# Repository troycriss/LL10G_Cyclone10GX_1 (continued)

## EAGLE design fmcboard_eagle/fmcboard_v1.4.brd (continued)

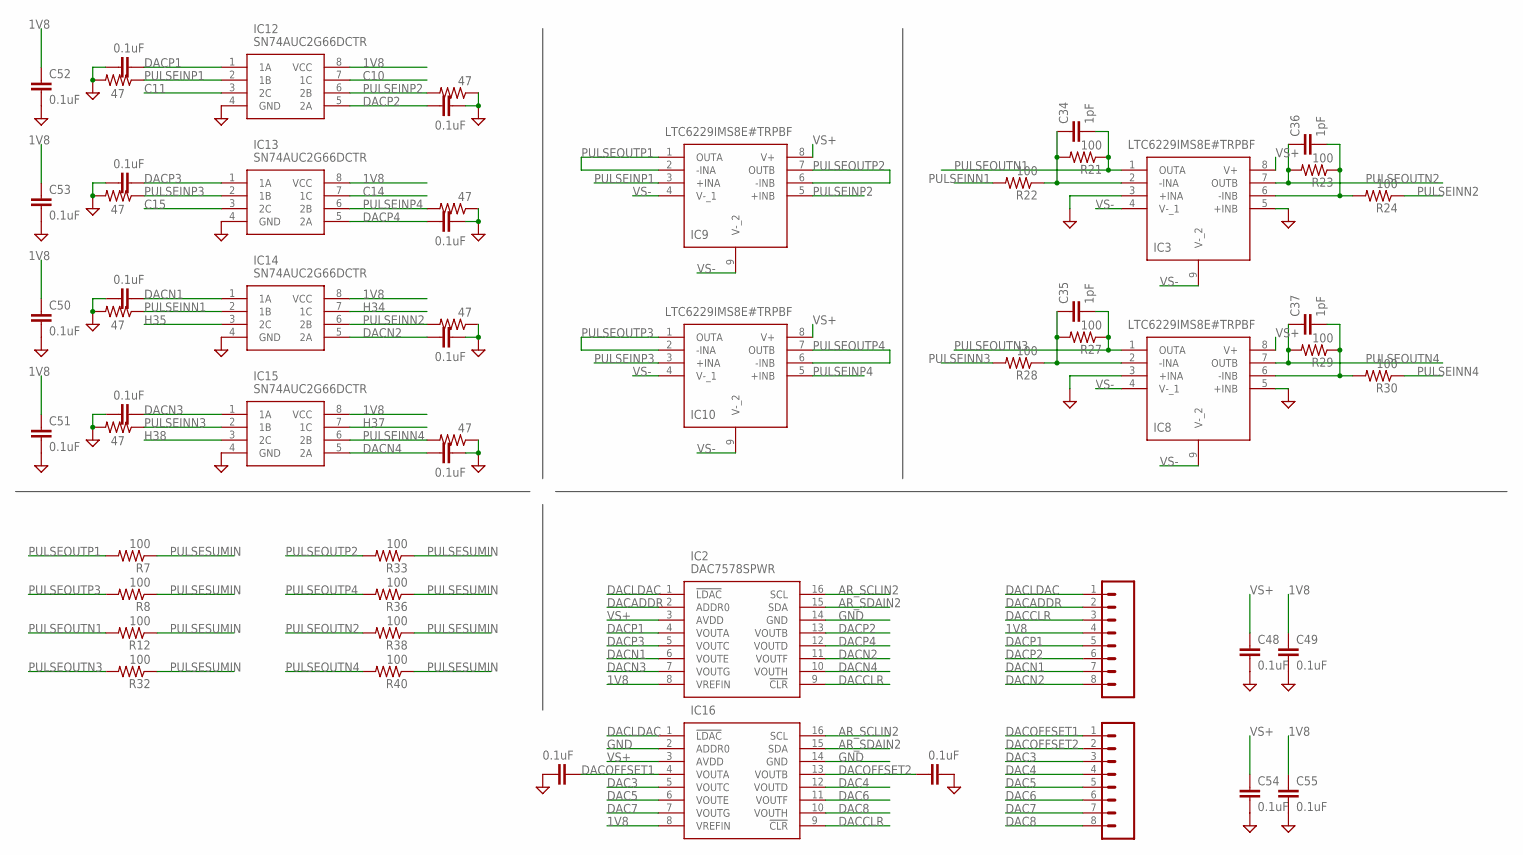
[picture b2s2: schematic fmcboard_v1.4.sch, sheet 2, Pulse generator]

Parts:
C34, C35, C36, C37: 1pF; 0805
C48, C49, C50, C51, C52, C53, C54, C55, C56, C57, C58, C59, C60, C61, C62, C63, C64, C65: 0.1uF; 0805
IC2, IC16: DAC7578SPWR; SOP65P640X120-16N
IC3, IC8, IC9, IC10: LTC6229IMS8E#TRPBF; SOP65P490X110-9N
IC12, IC13, IC14, IC15: SN74AUC2G66DCTR; SOP65P400X130-8N
J9, J10: 8pin; 1X08
R7, R8, R12, R21, R22, R23, R24, R27, R28, R29, R30, R32, R33, R36, R38, R40: 100; R0805
R37, R39, R41, R43, R44, R45, R46, R47: 47; R0805

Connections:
1V8: C49.1, C50.1, C51.1, C52.1, C53.1, C55.1, IC2.8 (VREFIN), IC12.8 (VCC), IC13.8 (VCC), IC14.8 (VCC), IC15.8 (VCC), IC16.8 (VREFIN), J9.4; also elsewhere on the board
AR_SCLIN2: IC2.16 (SCL), IC16.16 (SCL); also elsewhere on the board
AR_SDAIN2: IC2.15 (SDA), IC16.15 (SDA); also elsewhere on the board
C10: IC12.7 (1C); also elsewhere on the board
C11: IC12.3 (2C); also elsewhere on the board
C14: IC13.7 (1C); also elsewhere on the board
C15: IC13.3 (2C); also elsewhere on the board
DAC3: IC16.5 (VOUTC), J10.3
DAC4: IC16.12 (VOUTD), J10.4
DAC5: IC16.6 (VOUTE), J10.5
DAC6: IC16.11 (VOUTF), J10.6
DAC7: IC16.7 (VOUTG), J10.7
DAC8: IC16.10 (VOUTH), J10.8
DACADDR: IC2.2 (ADDR0), J9.2
DACCLR: IC2.9 (!CLR), IC16.9 (!CLR), J9.3
DACLDAC: IC2.1 (!LDAC), IC16.1 (!LDAC), J9.1
DACN1: C57.2, IC2.6 (VOUTE), IC14.1 (1A), J9.7
DACN2: C61.1, IC2.11 (VOUTF), IC14.5 (2A), J9.8
DACN3: C59.2, IC2.7 (VOUTG), IC15.1 (1A)
DACN4: C60.1, IC2.10 (VOUTH), IC15.5 (2A)
DACOFFSET1: C64.2, IC16.4 (VOUTA), J10.1; also elsewhere on the board
DACOFFSET2: C65.1, IC16.13 (VOUTB), J10.2; also elsewhere on the board
DACP1: C58.2, IC2.4 (VOUTA), IC12.1 (1A), J9.5
DACP2: C63.1, IC2.13 (VOUTB), IC12.5 (2A), J9.6
DACP3: C56.2, IC2.5 (VOUTC), IC13.1 (1A)
DACP4: C62.1, IC2.12 (VOUTD), IC13.5 (2A)
GND: C48.2, C49.2, C50.2, C51.2, C52.2, C53.2, C54.2, C55.2, C56.1, C57.1, C58.1, C59.1, C60.2, C61.2, C62.2, C63.2, C64.1, C65.2, IC2.14 (GND), IC3.3 (+INA), IC3.5 (+INB), IC8.3 (+INA), IC8.5 (+INB), IC12.4 (GND), IC13.4 (GND), IC14.4 (GND), IC15.4 (GND), IC16.2 (ADDR0), IC16.14 (GND), R37.1, R39.2, R41.1, R43.2, R44.2, R45.2, R46.1, R47.1; also elsewhere on the board
H34: IC14.7 (1C); also elsewhere on the board
H35: IC14.3 (2C); also elsewhere on the board
H37: IC15.7 (1C); also elsewhere on the board
H38: IC15.3 (2C); also elsewhere on the board
unnamed: C36.2, IC3.6 (-INB), R23.1, R24.2
unnamed: C35.1, IC8.2 (-INA), R27.2, R28.1
unnamed: C34.1, IC3.2 (-INA), R21.2, R22.1
unnamed: C37.2, IC8.6 (-INB), R29.1, R30.2
PULSEINN1: IC14.2 (1B), R22.2, R44.1
PULSEINN2: IC14.6 (2B), R24.1, R47.2
PULSEINN3: IC15.2 (1B), R28.2, R45.1
PULSEINN4: IC15.6 (2B), R30.1, R46.2
PULSEINP1: IC9.3 (+INA), IC12.2 (1B), R39.1
PULSEINP2: IC9.5 (+INB), IC12.6 (2B), R37.2
PULSEINP3: IC10.3 (+INA), IC13.2 (1B), R43.1
PULSEINP4: IC10.5 (+INB), IC13.6 (2B), R41.2
PULSEOUTN1: C34.2, IC3.1 (OUTA), R12.2, R21.1
PULSEOUTN2: C36.1, IC3.7 (OUTB), R23.2, R38.2
PULSEOUTN3: C35.2, IC8.1 (OUTA), R27.1, R32.2
PULSEOUTN4: C37.1, IC8.7 (OUTB), R29.2, R40.2
PULSEOUTP1: IC9.1 (OUTA), IC9.2 (-INA), R7.2
PULSEOUTP2: IC9.6 (-INB), IC9.7 (OUTB), R33.2
PULSEOUTP3: IC10.1 (OUTA), IC10.2 (-INA), R8.2
PULSEOUTP4: IC10.6 (-INB), IC10.7 (OUTB), R36.2
PULSESUMIN: R7.1, R8.1, R12.1, R32.1, R33.1, R36.1, R38.1, R40.1; also elsewhere on the board
VS+: C48.1, C54.1, IC2.3 (AVDD), IC3.8 (V+), IC8.8 (V+), IC9.8 (V+), IC10.8 (V+), IC16.3 (AVDD); also elsewhere on the board
VS-: IC3.4 (V-_1), IC3.9 (V-_2), IC8.4 (V-_1), IC8.9 (V-_2), IC9.4 (V-_1), IC9.9 (V-_2), IC10.4 (V-_1), IC10.9 (V-_2); also elsewhere on the board

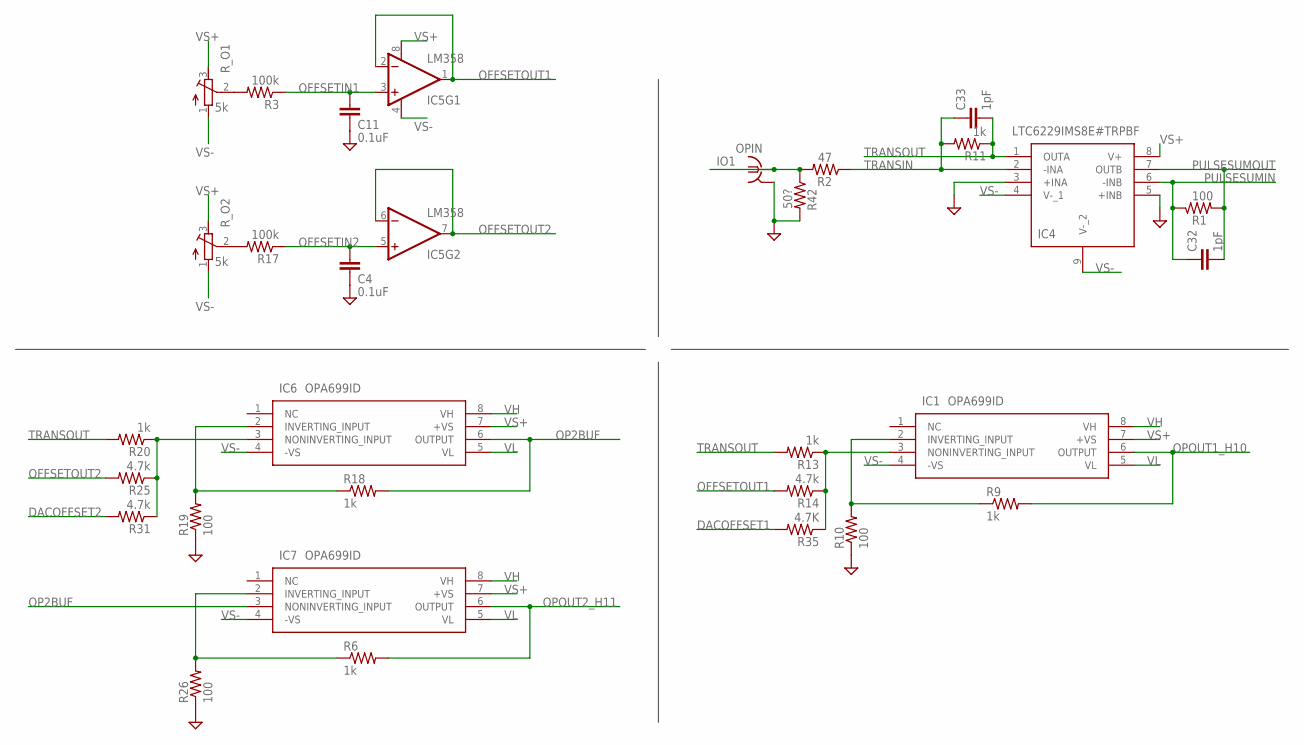
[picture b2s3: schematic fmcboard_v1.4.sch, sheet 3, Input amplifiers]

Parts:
C4, C11: 0.1uF; 0805
C32, C33: 1pF; 0805
IC1, IC6, IC7: OPA699ID; SOIC127P600X175-8N
IC4: LTC6229IMS8E#TRPBF; SOP65P490X110-9N
IC5: LM358; DIP08
OPIN: BU-SMB-V
R1, R10, R19, R26: 100; R0805
R2: 47; R0805
R3, R17: 100k; R0805
R6, R9, R11, R13, R18, R20: 1k; R0805
R14, R25, R31: 4.7k; R0805
R35: 4.7K; R0805
R42: 50?; R0805
R_O1, R_O2: 5k; RTRIM3296W

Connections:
DACOFFSET1: R35.2; also elsewhere on the board
DACOFFSET2: R31.2; also elsewhere on the board
GND: C4.2, C11.2, IC4.3 (+INA), IC4.5 (+INB), OPIN.2, OPIN.3 (2), OPIN.4 (2), OPIN.5 (2), R10.1, R19.1, R26.1, R42.2; also elsewhere on the board
IO1: OPIN.1, R2.2, R42.1; also elsewhere on the board
unnamed: IC1.3 (NONINVERTING_INPUT), R13.1, R14.1, R35.1
unnamed: R17.2, R_O2.2 (S)
unnamed: IC1.2 (INVERTING_INPUT), R9.1, R10.2
unnamed: R3.2, R_O1.2 (S)
unnamed: IC6.2 (INVERTING_INPUT), R18.1, R19.2
unnamed: IC6.3 (NONINVERTING_INPUT), R20.1, R25.1, R31.1
unnamed: IC7.2 (INVERTING_INPUT), R6.1, R26.2
OFFSETIN1: C11.1, IC5.3 (+IN), R3.1; also elsewhere on the board
OFFSETIN2: C4.1, IC5.5 (+IN), R17.1; also elsewhere on the board
OFFSETOUT1: IC5.1 (OUT), IC5.2 (-IN), R14.2
OFFSETOUT2: IC5.6 (-IN), IC5.7 (OUT), R25.2
OP2BUF: IC6.6 (OUTPUT), IC7.3 (NONINVERTING_INPUT), R18.2; also elsewhere on the board
OPOUT1_H10: IC1.6 (OUTPUT), R9.2; also elsewhere on the board
OPOUT2_H11: IC7.6 (OUTPUT), R6.2; also elsewhere on the board
PULSESUMIN: C32.1, IC4.6 (-INB), R1.1; also elsewhere on the board
PULSESUMOUT: C32.2, IC4.7 (OUTB), R1.2; also elsewhere on the board
TRANSIN: C33.1, IC4.2 (-INA), R2.1, R11.2
TRANSOUT: C33.2, IC4.1 (OUTA), R11.1, R13.2, R20.2; also elsewhere on the board
VH: IC1.8 (VH), IC6.8 (VH), IC7.8 (VH); also elsewhere on the board
VL: IC1.5 (VL), IC6.5 (VL), IC7.5 (VL); also elsewhere on the board
VS+: IC1.7 (+VS), IC4.8 (V+), IC5.8 (V+), IC6.7 (+VS), IC7.7 (+VS), R_O1.3 (E), R_O2.3 (E); also elsewhere on the board
VS-: IC1.4 (-VS), IC4.4 (V-_1), IC4.9 (V-_2), IC5.4 (V-), IC6.4 (-VS), IC7.4 (-VS), R_O1.1 (A), R_O2.1 (A); also elsewhere on the board

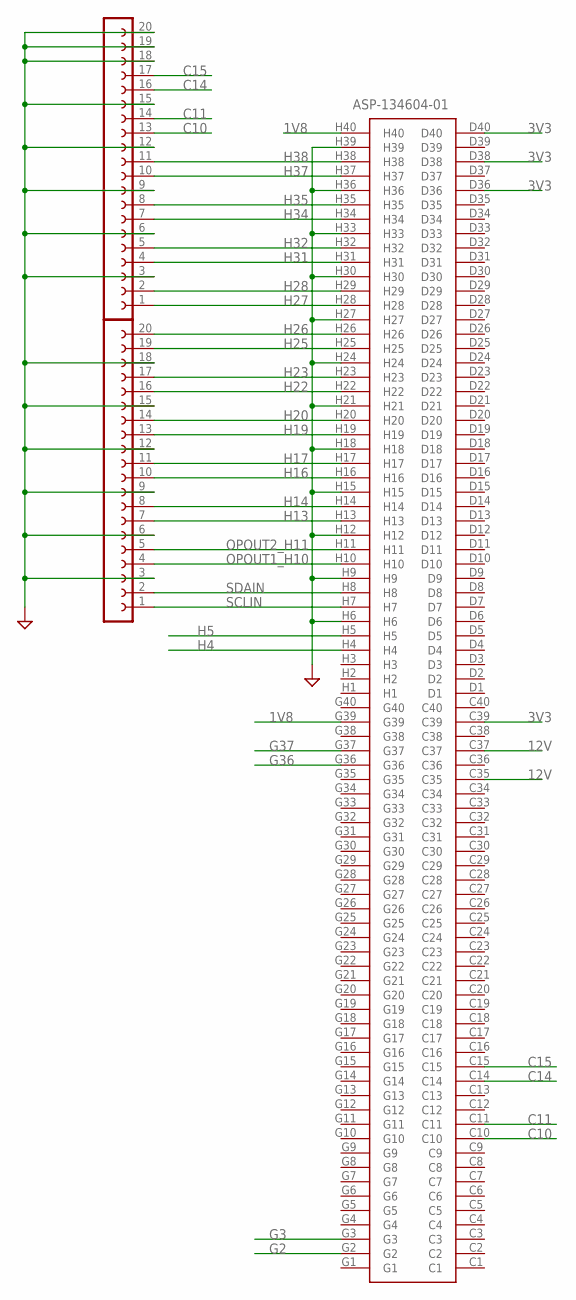
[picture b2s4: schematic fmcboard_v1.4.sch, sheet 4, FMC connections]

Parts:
J2: ASP-134604-01; ASP13460401
SV1, SV2: 20; FE20

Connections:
1V8: J2.G39, J2.H40; also elsewhere on the board
3V3: J2.C39, J2.D36, J2.D38, J2.D40; also elsewhere on the board
12V: J2.C35, J2.C37; also elsewhere on the board
C10: J2.C10, SV2.13; also elsewhere on the board
C11: J2.C11, SV2.14; also elsewhere on the board
C14: J2.C14, SV2.16; also elsewhere on the board
C15: J2.C15, SV2.17; also elsewhere on the board
G2: J2.G2; also elsewhere on the board
G3: J2.G3; also elsewhere on the board
G36: J2.G36; also elsewhere on the board
G37: J2.G37; also elsewhere on the board
GND: J2.H6, J2.H9, J2.H12, J2.H15, J2.H18, J2.H21, J2.H24, J2.H27, J2.H30, J2.H33, J2.H36, J2.H39, SV1.3, SV1.6, SV1.9, SV1.12, SV1.15, SV1.18, SV2.3, SV2.6, SV2.9, SV2.12, SV2.15, SV2.18, SV2.19, SV2.20; also elsewhere on the board
H4: J2.H4; also elsewhere on the board
H5: J2.H5; also elsewhere on the board
H13: J2.H13, SV1.7
H14: J2.H14, SV1.8
H16: J2.H16, SV1.10
H17: J2.H17, SV1.11
H19: J2.H19, SV1.13
H20: J2.H20, SV1.14
H22: J2.H22, SV1.16
H23: J2.H23, SV1.17
H25: J2.H25, SV1.19
H26: J2.H26, SV1.20
H27: J2.H28, SV2.1
H28: J2.H29, SV2.2
H31: J2.H31, SV2.4
H32: J2.H32, SV2.5
H34: J2.H34, SV2.7; also elsewhere on the board
H35: J2.H35, SV2.8; also elsewhere on the board
H37: J2.H37, SV2.10; also elsewhere on the board
H38: J2.H38, SV2.11; also elsewhere on the board
OPOUT1_H10: J2.H10, SV1.4; also elsewhere on the board
OPOUT2_H11: J2.H11, SV1.5; also elsewhere on the board
SCLIN: J2.H7, SV1.1; also elsewhere on the board
SDAIN: J2.H8, SV1.2; also elsewhere on the board

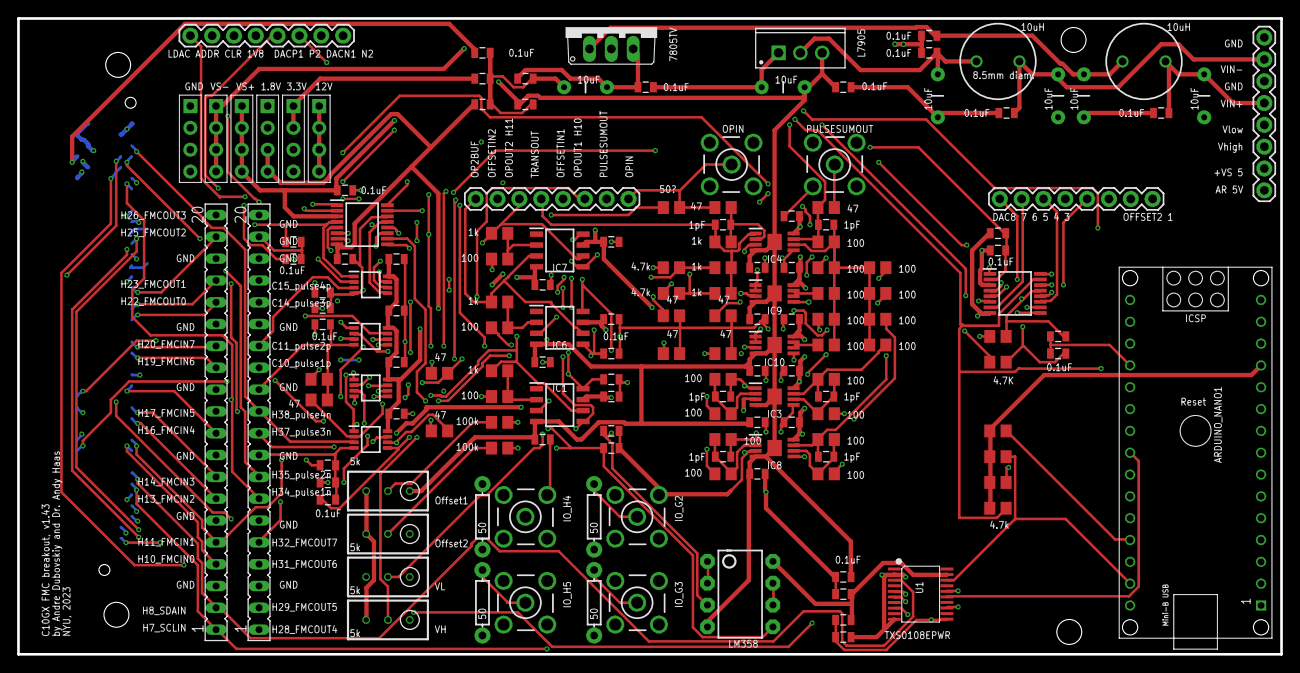
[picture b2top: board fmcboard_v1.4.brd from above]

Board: 4 copper layers, 147.0 x 74.0 mm, 160 parts (1 on the bottom side), 108 nets.

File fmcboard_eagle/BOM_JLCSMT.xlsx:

Comment | Designator | Footprint | JLCPCB Part #（optional）
0.1uF | C3, C4, C5, C6, C7, C8, C9, C10, C11, C12, C13, C14, C15, C16, C17, C18, C19, C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 | 0805
1 | ARDUINO_NANO1 | ARDUINO_NANO
100k | R3, R17 | R0805
10uF | C1, C2, C38, C39, C40, C41 | CAP-PTH-5MM
10uH | L1, L2 | 6000-XXXX-RC
1k | R1, R6, R7, R8, R9, R11, R12, R13, R18, R20, R21, R22, R23, R24, R27, R28, R29,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 | R0805
1pF | C32, C33, C34, C35, C36, C37 | 0805
20 | SV1, SV2 | FE20
100 | R10, R19, R26 | R0805
20k | R_O1, R_O2, R_VH, R_VL | RTRIM3296W
4.7k | R48, R49, R50, R51 | R0805
47 | R37, R39, R41, R43, R44, R45, R46, R47 | R0805
4k | R14, R25, R31, R35 | R0805
4p-2.54 | J3, J4, J6, J7, J8, J12 | H4-2.54
50 | R2, R34 | R0805
50 | R4, R5, R15, R16 | AXIAL-0.3
50? | R42 | R0805
7805TV | IC11 | TO220V
8pin | J1, J5, J9, J10 | 8-pin
ASP-134604-01 | J2 | ASP13460401
BU-SMB-V | IO_G2, IO_G3, IO_H4, IO_H5, OPIN, PULSESUMOUT | BU-SMB-V
DAC7578SPWR | IC2, IC16 | SOP65P640X120-16N
LM358 | IC5 | DIP08
LTC6229IMS8E#TRPBF | IC3, IC4, IC8, IC9, IC10 | SOP65P490X110-9N
OPA699ID | IC1, IC6, IC7 | SOIC127P600X175-8N
SN74AUC2G66DCTR | IC12, IC13, IC14, IC15 | SOP65P400X130-8N
STMICROELECTRONICS_L7905ACVSTMICROELECTRONICS_L7905ACV_0_0 | U2 | STMICROELECTRONICS_L7905ACV_0
TXS0108EPWR | U1 | TSSOP20-0.65-6.5X4.4MM

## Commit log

2023-03-08 turn off tx if pin 2 at gnd
2023-03-08 take 8 inputs from FMC and add to ethernet data
2023-03-09 try adding IP and UDP headers
2023-03-10 count bytes also during ip123
2023-03-10 send ethII header, and fix udp length calculation
2023-03-10 wireshark UDP
2023-03-13 docs
2023-03-13 add sketch of fmcboard
2023-03-13 fifo test
2023-03-13 fifo test 2
2023-03-13 fifo test 3
2023-03-13 fifo test 4
2023-03-13 op amp
2023-03-14 fifo working sort of
2023-03-14 with test data
2023-03-14 opa699 datasheet
2023-03-14 with more clocks
2023-03-14 just need to close timing
2023-03-15 added two op amps to condition input and added GPIO breakout
2023-03-15 ripup'd all routes
2023-03-15 timing closed
2023-03-15 board v1 work with Andre
2023-03-15 Variable IP address
2023-03-16 fix the ip checksum and make the udp one 0 always
2023-03-16 fix the ip checksum more and put seq_num, packet num, and queue length in the data
2023-03-16 Clear fifo at start of data taking
2023-03-16 Send 1516 bytes
2023-03-16 Decode and print
2023-03-16 remove temp files from git
2023-03-16 remove sim files
2023-03-16 sample nbitstosample bits (1 by default)
2023-03-16 first draft of pcb routing
2023-03-16 add output clock at 156.25 MHz / 16, switch eth1 to another 8 inputs
2023-03-16 fmcboard v1 submitted
2023-03-17 fmcboard v1 submitted again, with board outline and stencil
2023-03-19 get ip data length right
2023-03-20 read 1 extra after clearing fifo
2023-03-20 blink
2023-03-20 update pcaps
2023-03-22 remove do_test_data option, and close timing
2023-03-22 add metastability protection to 3 for fifo
2023-03-23 cleanup pin warnings
2023-03-23 pdf of schematic
2023-03-27 add zip
2023-03-27 add i2c lib
2023-03-27 switch sda scl 5v to 1.8
2023-03-28 Board v1.1
2023-03-28 Add fmc doc
2023-03-28 Add sch printout v1.1 board
2023-04-05 switch sda and scl to match board v1.1
2023-04-05 Change resistors and labels
2023-04-06 ignore qws
2023-04-06 Add more power connections to FMC header
2023-04-06 Update resistor values
2023-04-07 add lm358 op amp buffer for offset
2023-04-07 Update gain resistor values
2023-04-08 use bss138 level shifting
2023-04-08 switch to C26 and C27
2023-04-10 Revert "switch to C26 and C27"
    This reverts commit 01cab55b1ab11df4a8fa88617da78cc3c47528a8.
2023-04-10 Revert "use bss138 level shifting"
    This reverts commit dd6467e355429a32c42db6855984b6cad7435a14.
2023-04-11 Label fmc in/out make fmcout0-3 equal to fmcin0-3, for debugging/testing
2023-04-12 v1.2 draft, add transimpedance amp, 2 gains and offsets, pulse outputs, etc.
2023-04-13 Before routing
2023-04-13 v1.2
2023-04-13 v1.2 gerbers
2023-04-13 v1.21 make exposed pads VS- not GND, divide voltage before op amp buffers, add op amp decoupling caps, improve layout
2023-04-13 v1.21
2023-04-19 Add inputs and outputs for FMC v1.21 board
2023-04-25 Fixes for v1.21, amps etc
2023-04-25 Tune the trans amp gain and compensation
2023-04-26 cleaned up a bit, added topgnd cutouts still need to fix power, layout of amp feedback, and route
2023-04-26 did power still need to fix layout of amp feedback, and route
2023-04-26 minor
2023-04-27 most routing done by hand
2023-04-27 v1.3
2023-04-29 Fix feedback compensation caps on neg pulse amps, new footprint for L7905
2023-05-26 added pulsecontroller and console commands to adjust pulse width. Not working yet.
2023-05-31 Added pulse/PulseController.v file and console command for pause duration. Changed assignments in pulser to async. Waveform is no longer "shaky"
2023-05-31 Using slower clock now ("fast1_clk")
2023-06-01 Using faster clock now ("fast2_clk")
2023-06-01 increase udp buff size
2023-06-02 localhost to ""
2023-06-02 LED BUILTING should be an output
2023-06-02 Note ethernet card settings
2023-06-02 Print only 1/100 packets. This keeps up with nbitstosend==1 traffic on 10G.
2023-06-08 Added lots of pulses (12 total). Doesn't work yet.
2023-06-09 fixed 12 pulse generator
2023-06-09 Fix compiler warnings and close timing
2023-06-20 printing out trigger and signal in two columns
2023-06-20 random bit parser and averaging works (slowly)
2023-06-20 bit parser works quickly now, with struct.unpack()
2023-07-06 improved and simplified UDPlistner.py
2023-07-06 added preemptive "sanity check" read pulse between reset and write. set trigger to a separate reg.
2023-07-12 collected first data
2023-07-26 refactoring FIFO to filter out irrelevant bits on FPGA side
2023-07-28 v1.4 has DACs and switches for pulses and offset adjustments
2023-07-29 add pics
2023-07-29 v1.41 fix VS+ -> 1V8 for switches
2023-07-29 v1.42 add 100 Ohm resistors to GND for when switches are off (V should go to GND fast!)
2023-08-03 1.43 add caps on dac outs
2023-08-03 1.43 switch SDA and SCL for DACs to A4/5, add 4.7k pullups on SDA/SCL lines
2023-08-09 Add DAC test arduino code
2023-08-09 v1.43 100 -> 47 Ohm for pulses
2023-08-09 Put all components on top
2023-08-09 v1.43 ordered
2023-08-15 100 Ohm neg pulse and neg sum feedback resistors 4.7k->1k transimpedance resistor
2023-08-18 20k -> 5k pots
2023-08-18 examples for talking to both chips
2023-08-18 little more doc
2023-08-18 little more doc again
2023-08-21 first attempt at filtering out reset errors
2023-08-21 added console command for offset to check for reset error
2023-09-07 Gain resistors updated to 1k, 100
2023-09-08 Initial v1.50, with inverters going to switches to gnd
2023-09-09 Switch to 74LVC2GU04 inverters
2023-09-15 Revert "Switch to 74LVC2GU04 inverters"
    This reverts commit 0d5c0f9254668030431faa83bc2596f2b624104f.
2023-09-15 Switch to 74AUP2GU04GW inverters
2023-09-15 Minor BOM update
2023-09-15 Rotate switches in cpl
2023-09-15 Add docs
2023-09-16 Use SMT LM358
2023-09-18 v1.51 : Add 1k resistors before DAC caps (to prevent oscillations), and make the caps 470pF -> 1uF
2023-09-19 v1.6 : new pulse scheme
2023-09-19 remove 47 ohm resistors to gnd
2023-09-19 make gnd switches on N inverters
2023-09-19 100 ohm between dac and caps
2023-09-19 routed
2023-09-19 v1.6
2023-09-19 v1.51
2023-09-19 v1.6 with AMS1117-1.8
2023-09-21 initial
2023-09-21 fancier
2023-09-21 better layout
2023-09-21 routed 1.61
2023-09-26 find and print peaks
2023-09-26 smd inductors
2023-09-27 route power better
2023-09-29 v1.61: Fix 1v8- 1k->330 fo 16 100->330 for 9 1pF and 10k pulldown on opin 10k pulldowns on neg pulse inputs
2023-09-29 v1.61: Add OPA695 for transimpedance and first stage of opin amp
2023-09-30 ordered
2023-10-04 use 1.8- and gnd for negative switches to gnd add 100 ohm resistors to inverting opa695s
2023-10-04 remove old stuff
2023-10-04 for production
2023-10-05 add dac pulse offsets + and -
2023-10-05 cleanup and rename to 1.6 for v1.62
2023-10-12 change a few resistors for 1.8- stability
2023-10-18 100pF decoupling added to opa695's, and wider traces Routing near 695's 100ohm and 470 to opa699's for better bw
2023-10-22 add cj7805 and cj7905 and 1.8v- regs
2023-10-23 Transout near pin, after 100R Pulse sum out near to sma instead, after 100R Output of first amp after transout (op1buf), after 100R
    100pF for all the fast amps
    100R at end of h11 (and 1k at end of h10)
2023-10-23 Power routed
2023-10-23 Better 7805 7905 footprints
2023-10-23 mostly routed
2023-10-23 routed v1.63
2023-10-31 new serial arduino code
2023-11-01 -1.8V 100uF cap for stability 330 -> 470 for 695 pulseout 330 -> 470 for inputs to pulseout Replace initial 695 with 699 for lower noise, and feedback 470 to 1k Increase gain for opbuf and h10, 470 -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
2023-11-02 v1.64 add test 2.6k resistor routed, better gnd connections
2023-11-02 v1.64
2023-11-07 v1.65 4.7k -> 100 for input termination 2.6k -> 1-3k for test resistor 100 to gnd on h10/11 h10 -> 10 ohm -> h11 h27/28 -> h28/29
2023-11-08 v1.65 add gnds to fmc and extra C connections
2023-11-08 cleanup
2023-11-13 reduced pulser segments to 7. noticed that one of the signal_out bits doesn't work (does not get through the dacs). this is the bit 00001000.
2023-11-14 v1.65 C26 and C27 to A0 and A1 on arduino Remove level shifter, replace with 4.7k resistors
2024-02-13 timing closure (ignore clk0 to clk3 paths)
2024-03-28 reverting old i2c-ethernet sketch
2024-04-04 added all python scripts and restored working firmware
2024-04-05 from Andre
2024-04-15 commit xor changes not working
2024-04-15 Added extra 4 DAC outputs, 2 positive and 2 negative Copies of pulse out and amp out to sma - TODO
2024-04-16 Added extra 4 DAC outputs, 2 positive and 2 negative Move to 0402 R and C Copies of pulse out and amp out to sma - TODO
2024-04-16 Added extra 4 DAC outputs, 2 positive and 2 negative Move all to 0402 R and C Replace 100uF with 10 10uF Copies of pulse out and amp out to sma - TODO
2024-04-16 Added extra 4 DAC outputs, 2 positive and 2 negative Move all to 0402 R and C Replace 100uF with 10 10uF Remove dacoffset variable resistor, replace with DAC N Set VH and VL to 1.8 and GND Copies of 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
2024-04-16 Added extra 4 DAC outputs, 2 positive and 2 negative Move all to 0402 R and C Replace 100uF with 10 10uF Remove dacoffset variable resistor, replace with DAC N Set VH and VL to 1.8 and GND Copies of 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
2024-04-16 power routed, plus gnd
2024-04-17 schematics pdfs
2024-04-17 cosmetic updates to v1.65
2024-04-17 schmatics
2024-04-17 with smaller 0402
2024-04-18 and power +-7 onboard laid out
2024-04-18 power and gnd routed (with vias)
2024-04-18 1.65s
2024-04-19 remove LCSC 17415 0805 bug
2024-04-19 add bottom FMC connector
2024-04-19 sch pdf
2024-04-19 extra 10 uF caps
2024-04-22 working xor on firmware
2024-04-22 v1.652s Add C18 C19 C22 C23 pulse out holes Add C26 C27 SDAIN SCLIN holes
2024-04-24 v1.652s 0805 test resistor instead of 0402
2024-04-24 add opa695 doc
2024-04-24 fix VIN-
2024-04-24 remove pulsein hole
2024-04-25 remove sdain sclin c26 c27 holes clean up +-7 V schematic
2024-04-25 0805 10uF
2024-04-25 move 1.65s to 1.6
2024-04-25 tantalum 100uF
2024-04-30 v1.66 for test of +- power
2024-04-30 0805 25V caps for 12V And double them for Vin to Vin- (12V+7V)
2024-05-02 Tant only on 1.8- regulator
2024-05-02 v1.67
2024-05-03 V holes
2024-05-03 smd headers
2024-05-06 Revert "smd headers"
    This reverts commit 89ab3707157d78c83d60aa2d6a39565f5008c414.
2024-05-06 connect 12V to VIN and AR_5V to VS+
2024-05-06 minor routing
2024-05-08 add buffered opout and pulseout smas
2024-05-08 polarity of 2.2uF tant cap
2024-05-08 v1.68
2024-05-10 minor, 2x4 holes, routing cleanup
2024-05-16 added xor and xor toggle
2024-06-06 on-board I2C control in progress (DAC works, Ethernet does not work)
2024-06-10 i2c working
2024-06-14 remove arduino, expose SCL/SDA from FPGA
2024-06-14 add level shifting
2024-06-14 v1.7
2024-06-18 caps
2024-06-18 compress board
2024-06-18 added ethernet-on i2c to the cyclone
2024-06-19 changes from Andre for i2c
2024-06-21 add some holes for scl/sda scl2/sda2
2024-06-24 added parametric dacwrite generation (by chip id, dac channel, and voltage)
2024-07-15 updated i2c generator and added feedback script, compiles but not working
2024-07-17 pulse feedback and i2c updates, not yet working
2024-07-17 pulse adjust module added in top
2024-07-24 basic pulse feedback working
2024-07-24 fixed i2c bug and added intervals to pulse adjustments
2025-06-17 XOR working, working on inverting pulses
2025-06-19 adding polarity tcl command on st_gen
2025-06-19 instructions word docx
